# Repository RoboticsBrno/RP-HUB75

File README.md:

# RP2350 HUB75 Driver

Deska pro řízení HUB75 displejů založená na čipu [RP2350](https://www.raspberrypi.com/documentation/microcontrollers/silicon.html#rp2350)

<div style="display:grid; grid-template-columns:repeat(auto-fit,minmax(160px,1fr)); gap:1rem; align-items:start;">
    <figure>
        
        <figcaption>Front</figcaption>
    </figure>
    <figure>
        
        <figcaption>Back</figcaption>
    </figure>
</div>

Firmware a jeho dokumentace může být nalezen ve složce `sw/fw`. Mini driver pro pužití displaje pomocí USB je ve složce `sw/rawd`.

## Pinout

### Displej

| RP2350 | Displej | Displej | RP2350 |
|---:|:---|---:|:---|
| IO0  | R1  | G1  | IO1  |
| IO2  | B1  | GND | GND  |
| IO3  | R2  | G2  | IO4  |
| IO5  | B2  | E   | IO6  |
| IO7  | A   | B   | IO8  |
| IO9  | C   | D   | IO10 |
| IO11 | CLK | LAT | IO12 |
| IO13 | OE  | GND | GND  |

### Konektor

!!! note
    Je možno použít QSPI nebo SPI, v tom případě musí být TX na MISO/RX pinu master desky!
    
| Konektor (pin) | Signál | RP2350 |
|---:|---|:---|
| 1  | GND | GND  |
| 2  | 5V  | 5V   |
| 3  | 5V  | 5V   |
| 4  | D0  | IO19 |
| 5  | D1  | IO20 |
| 6  | D2  | IO21 |
| 7  | D3  | IO22 |
| 8  | GND | GND  |
| 9  | CS  | IO23 |
| 10 | CK  | IO24 |

### Extra konektor
- Na desce jsou vyvedené 2 extra datové piny na kterých je přístupné I2C a UART pro další rozšíření. (není implementováno)

| Pin | I2C | UART |
|---:|---|---|
| 14  | SDA  | TX  |
| 15  | SCL  | RX  |

### DBG & PWR Led
- Debug/status led - IO18
- Power led - 3V3

## Licence
Celý repositář je licencován pod MIT licencí s výjimkou složky `sw/fw`, která spadá pod licenci BSD-3-Clause.

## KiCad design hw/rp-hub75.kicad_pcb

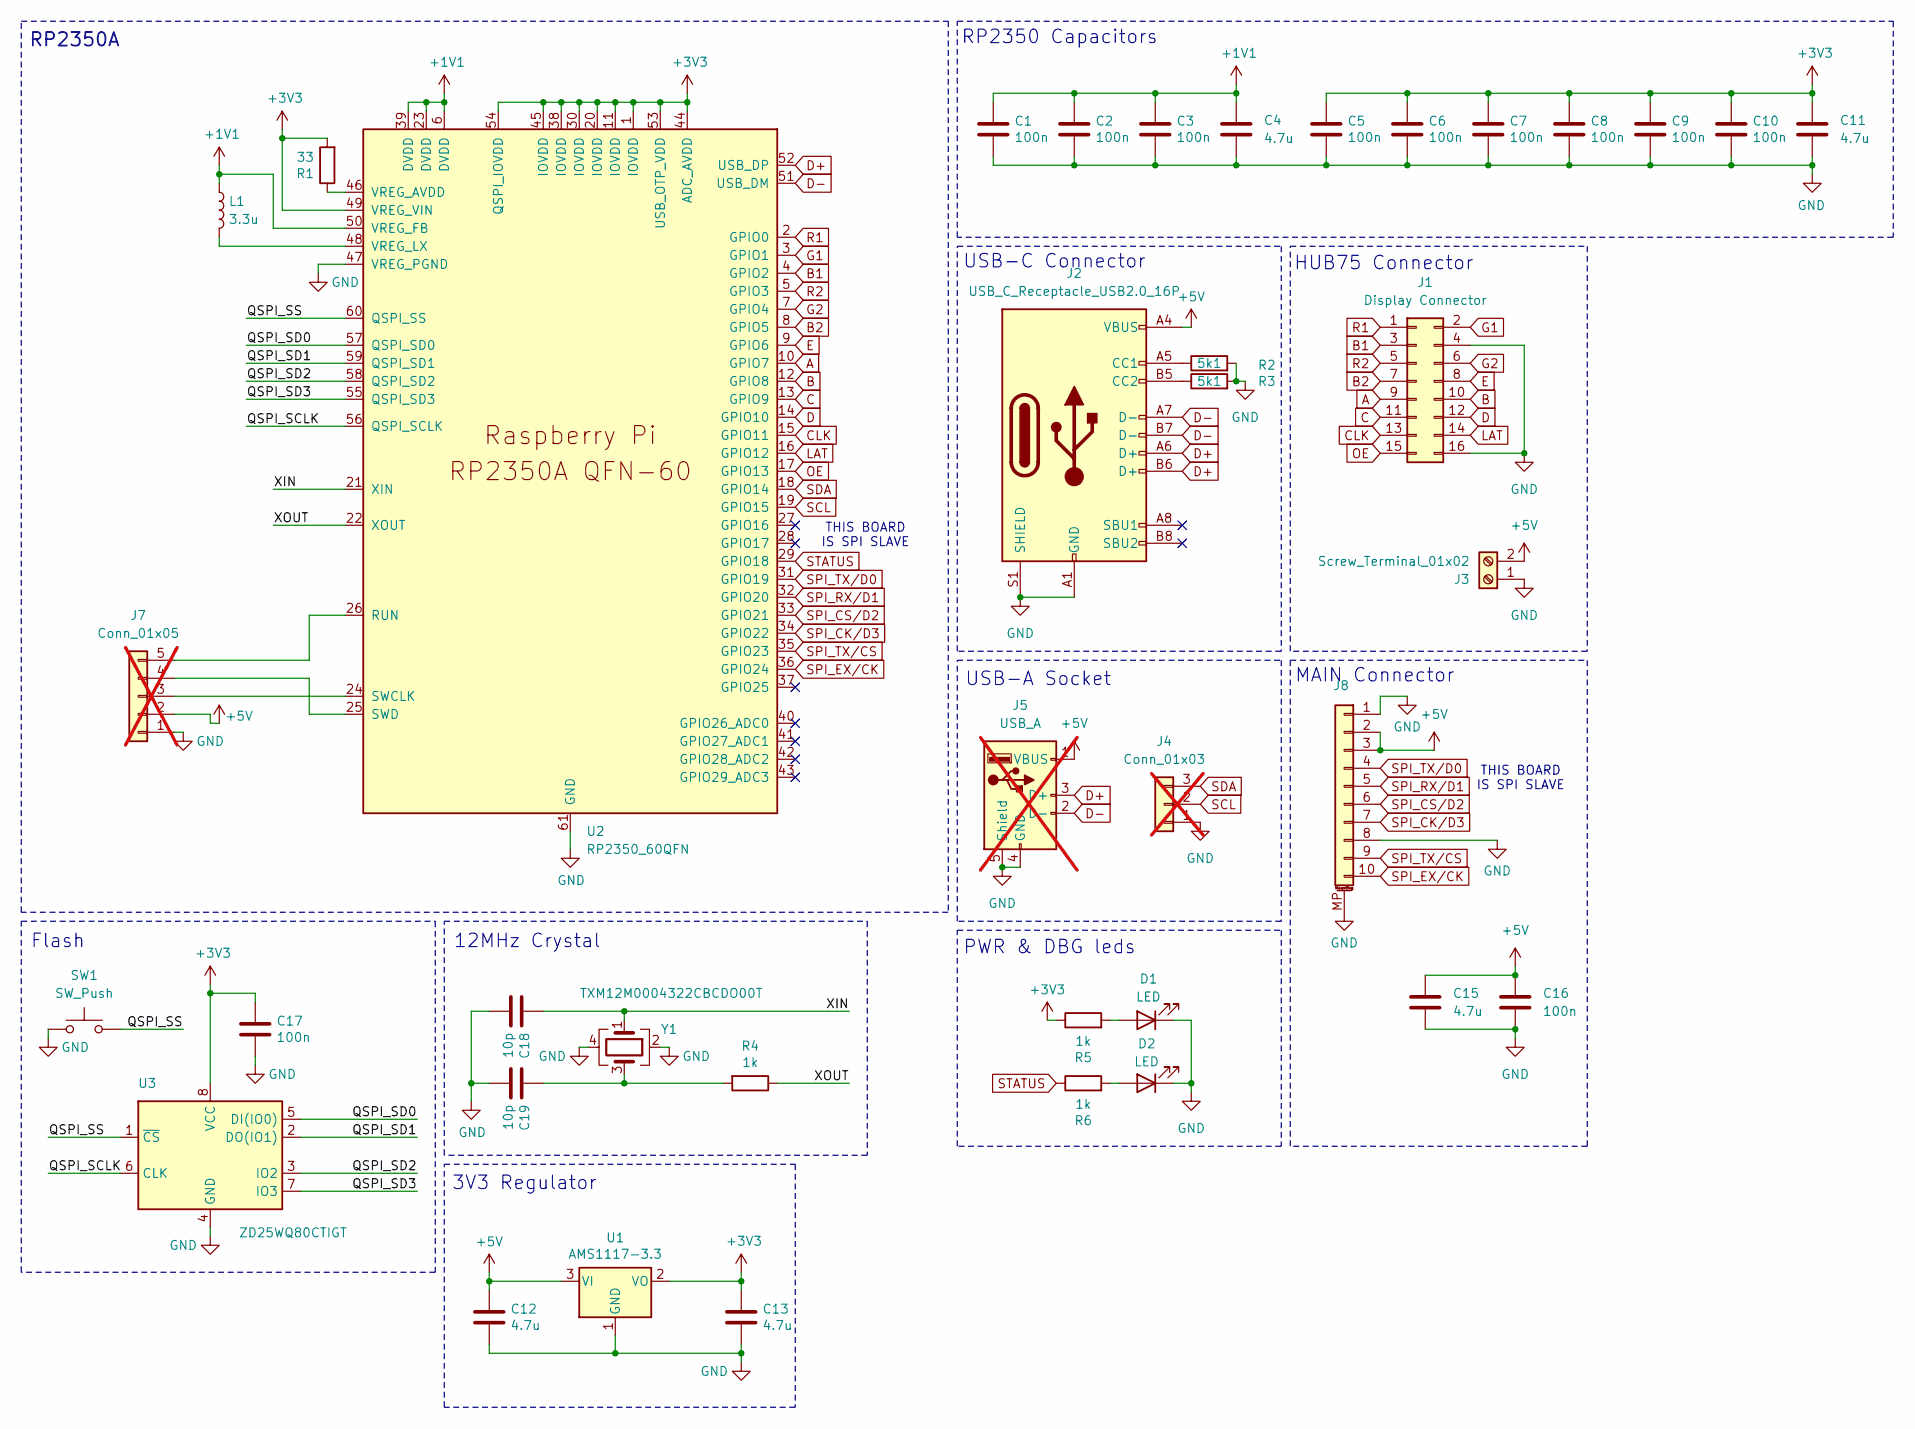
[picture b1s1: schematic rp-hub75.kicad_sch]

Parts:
C1, C2, C3, C5, C6, C7, C8, C9, C10, C16, C17: 100n; C_0402_1005Metric; LCSC C1525
C4, C11, C12, C13, C15: 4.7u; C_0805_2012Metric; LCSC C1779
C18, C19: 10p; C_0402_1005Metric; LCSC C32949
D1, D2: LED; LED_0805_2012Metric; LCSC C84256
J1: Display Connector; PinSocket_2x08_P2.54mm_Vertical; LCSC C30734
J2: USB_C_Receptacle_USB2.0_16P; USB_C_Receptacle_G-Switch_GT-USB-7010ASV; LCSC C2988369
J3: Screw_Terminal_01x02; TerminalBlock_Phoenix_MKDS-1,5-2-5.08_1x02_P5.08mm_Horizont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; LCSC C8465
J4: Conn_01x03; PinHeader_1x03_P2.54mm_Vertical; not fitted
J5: USB_A; USB_A_Kycon_KUSBX-AS1N-B_Horizontal; LCSC C2346; not fitted
J7: Conn_01x05; PinHeader_1x05_P2.54mm_Vertical; not fitted
J8: ZX-XH2.54-10PWT; JST-XH-SMD-10Pin; LCSC C7429679
L1: 3.3u; L_1008_2520Metric_Pad1.43x2.20mm_HandSolder; LCSC C337916
R1: 33; R_0402_1005Metric; LCSC C25105
R2, R3: 5k1; R_0402_1005Metric; LCSC C25905
R4, R5, R6: 1k; R_0402_1005Metric; LCSC C11702
SW1: SW_Push; SW_SPST_TS-1088-xR025; LCSC C720477
U1: AMS1117-3.3; SOT-223-3_TabPin2; LCSC C6186
U2: RP2350_60QFN; RP2350-QFN-60-1EP_7x7_P0.4mm_EP3.4x3.4mm_ThermalVias; LCSC C42411118
U3: ZD25WQ80CTIGT; SOIC-8_3.9x4.9mm_P1.27mm; LCSC C7525143
Y1: TXM12M0004322CBCDO00T; Crystal_SMD_3225-4Pin_3.2x2.5mm; LCSC C362368

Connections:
+1V1: C1.1, C2.1, C3.1, C4.1, L1.1, U2.6 (DVDD), U2.23 (DVDD), U2.39 (DVDD), U2.50 (VREG_FB)
+3V3: C5.1, C6.1, C7.1, C8.1, C9.1, C10.1, C11.1, C13.1, C17.1, R1.2, R5.1, U1.2 (VO), U2.1 (IOVDD), U2.11 (IOVDD), U2.20 (IOVDD), U2.30 (IOVDD), U2.38 (IOVDD), U2.44 (ADC_AVDD), U2.45 (IOVDD), U2.49 (VREG_VIN), U2.53 (USB_OTP_VDD), U2.54 (QSPI_IOVDD), U3.8 (VCC)
+5V: C12.1, C15.1, C16.1, J2.A4 (VBUS), J2.A9 (VBUS), J2.B4 (VBUS), J2.B9 (VBUS), J3.2, J5.1 (VBUS), J7.2, J8.2, J8.3, U1.3 (VI)
/QSPI_SCLK: U2.56 (QSPI_SCLK), U3.6 (CLK)
/QSPI_SD0: U2.57 (QSPI_SD0), U3.5 (DI(IO0))
/QSPI_SD1: U2.59 (QSPI_SD1), U3.2 (DO(IO1))
/QSPI_SD2: U2.58 (QSPI_SD2), U3.3 (IO2)
/QSPI_SD3: U2.55 (QSPI_SD3), U3.7 (IO3)
/QSPI_SS: SW1.2, U2.60 (QSPI_SS), U3.1 (~CS)
/XIN: C18.1, U2.21 (XIN), Y1.1
/XOUT: R4.1, U2.22 (XOUT)
A: J1.9, U2.10 (GPIO7)
B: J1.10, U2.12 (GPIO8)
B1: J1.3, U2.4 (GPIO2)
B2: J1.7, U2.8 (GPIO5)
C: J1.11, U2.13 (GPIO9)
CLK: J1.13, U2.15 (GPIO11)
D: J1.12, U2.14 (GPIO10)
D+: J2.A6 (D+), J2.B6 (D+), J5.3 (D+), U2.52 (USB_DP)
D-: J2.A7 (D-), J2.B7 (D-), J5.2 (D-), U2.51 (USB_DM)
E: J1.8, U2.9 (GPIO6)
G1: J1.2, U2.3 (GPIO1)
G2: J1.6, U2.7 (GPIO4)
GND: C1.2, C2.2, C3.2, C4.2, C5.2, C6.2, C7.2, C8.2, C9.2, C10.2, C11.2, C12.2, C13.2, C15.2, C16.2, C17.2, C18.2, C19.2, D1.1 (K), D2.1 (K), J1.4, J1.16, J2.A1 (GND), J2.A12 (GND), J2.B1 (GND), J2.B12 (GND), J2.S1 (SHIELD), J3.1, J4.1, J5.4 (GND), J5.5 (Shield), J7.1, J8.1, J8.8, J8.MP (MountPin), R2.2, R3.2, SW1.1, U1.1 (GND), U2.47 (VREG_PGND), U2.61 (GND), U3.4 (GND), Y1.2, Y1.4
LAT: J1.14, U2.16 (GPIO12)
unnamed: C19.1, R4.2, Y1.3
unnamed: D1.2 (A), R5.2
unnamed: D2.2 (A), R6.2
unnamed: J2.A5 (CC1), R2.1
unnamed: J2.B5 (CC2), R3.1
unnamed: J7.3, U2.24 (SWCLK)
unnamed: J7.4, U2.25 (SWD)
unnamed: J7.5, U2.26 (RUN)
unnamed: R1.1, U2.46 (VREG_AVDD)
unnamed: L1.2, U2.48 (VREG_LX)
OE: J1.15, U2.17 (GPIO13)
R1: J1.1, U2.2 (GPIO0)
R2: J1.5, U2.5 (GPIO3)
SCL: J4.2, U2.19 (GPIO15)
SDA: J4.3, U2.18 (GPIO14)
SPI_CK/D3: J8.7, U2.34 (GPIO22)
SPI_CS/D2: J8.6, U2.33 (GPIO21)
SPI_EX/CK: J8.10, U2.36 (GPIO24)
SPI_RX/D1: J8.5, U2.32 (GPIO20)
SPI_TX/CS: J8.9, U2.35 (GPIO23)
SPI_TX/D0: J8.4, U2.31 (GPIO19)
STATUS: R6.1, U2.29 (GPIO18)

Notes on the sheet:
THIS BOARD IS SPI SLAVE
HUB75 Connector
USB-A Socket
12MHz Crystal
PWR & DBG leds
USB-C Connector
3V3 Regulator
Flash
RP2350A
RP2350 Capacitors
MAIN Connector

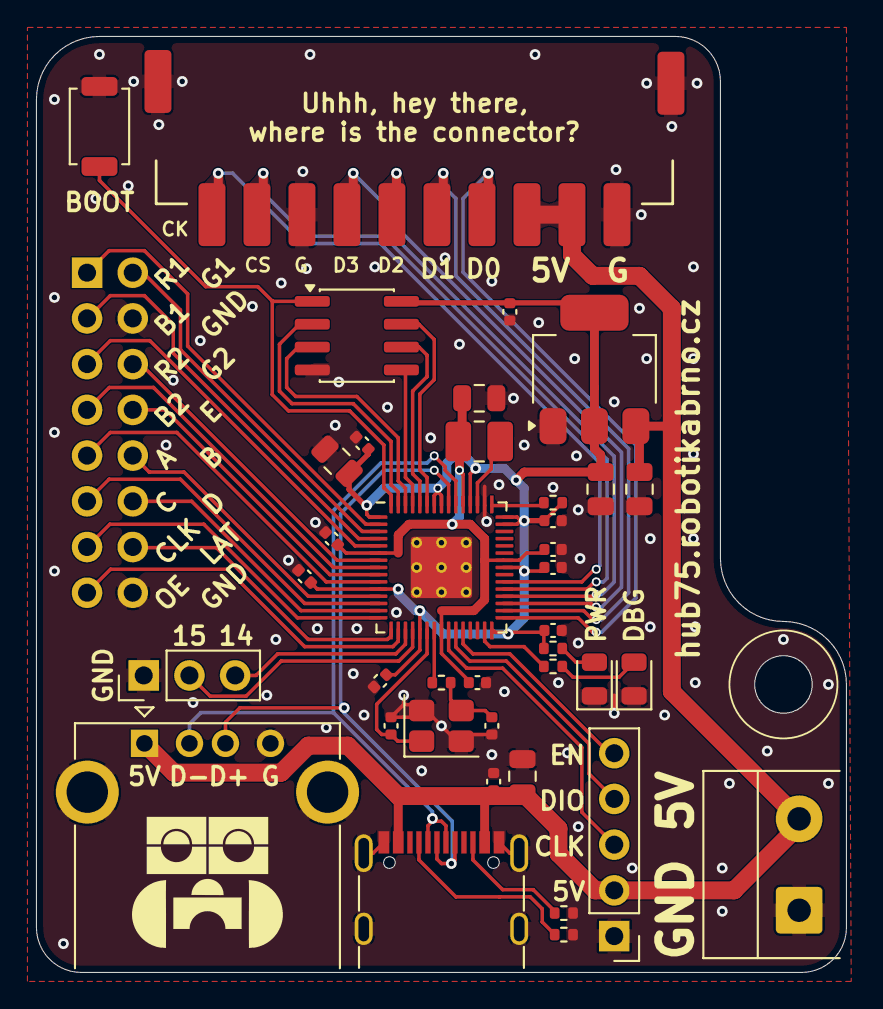
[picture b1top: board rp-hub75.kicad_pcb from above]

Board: 2 copper layers, 45.0 x 52.0 mm, 39 parts (1 on the bottom side), 47 nets.

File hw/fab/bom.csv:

Comment,Designator,Footprint,LCSC
ZD25WQ80CTIGT,U3,Package_SO:SOIC-8_3.9x4.9mm_P1.27mm,C7525143 
100n,"C1,C2,C3,C5,C6,C7,C8,C9,C10,C16,C17",Capacitor_SMD:C_0402_1005Metric,C1525
4.7u,"C4,C11,C12,C13,C15",Capacitor_SMD:C_0805_2012Metric,C1779
10p,"C18,C19",Capacitor_SMD:C_0402_1005Metric,C32949
USB_C_Receptacle_USB2.0_16P,J2,Connector_USB:USB_C_Receptacle_G-Switch_GT-USB-7010ASV,C2988369
RP2350_60QFN,U2,RP2350_60QFN_minimal:RP2350-QFN-60-1EP_7x7_P0.4mm_EP3.4x3.4mm_ThermalVias,C42411118 
Screw_Terminal_01x02,J3,"TerminalBlock_Phoenix:TerminalBlock_Phoenix_MKDS-1,5-2-5.08_1x02_P5.08mm_Horizontal",C8465
33,R1,Resistor_SMD:R_0402_1005Metric,C25105
LED,"D1,D2",LED_SMD:LED_0805_2012Metric,C84256
1k,"R4,R5,R6",Resistor_SMD:R_0402_1005Metric,C11702
5k1,"R2,R3",Resistor_SMD:R_0402_1005Metric,C25905
SW_Push,SW1,Button_Switch_SMD:SW_SPST_TS-1088-xR025,C720477
Display Connector,J1,Connector_PinSocket_2.54mm:PinSocket_2x08_P2.54mm_Vertical,C30734
3.3u,L1,Inductor_SMD:L_1008_2520Metric_Pad1.43x2.20mm_HandSolder,C337916
TXM12M0004322CBCDO00T,Y1,Crystal:Crystal_SMD_3225-4Pin_3.2x2.5mm,C362368
AMS1117-3.3,U1,Package_TO_SOT_SMD:SOT-223-3_TabPin2,C6186
ZX-XH2.54-10PWT,J8,Library:JST-XH-SMD-10Pin,C7429679

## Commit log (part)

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2025-10-29 Add files
2025-10-29 Deployed f63b39d with MkDocs version: 1.6.0
2025-10-29 docs: update readme
2025-10-29 Deployed 3daee73 with MkDocs version: 1.6.0
2025-11-01 WIP add fw, test-sw
2025-11-01 Deployed 836db96 with MkDocs version: 1.6.0
2025-11-01 hw: edit DBG connector, new capacitor
2025-11-05 update gitignore to fork
2025-11-05 wip: add first dev version of code
2025-11-05 feat: port moving circle from JohnieWalker
2025-11-05 feat: port platformer from JohnieWalker
2025-11-05 Deployed aa3a737 with MkDocs version: 1.6.0
2025-11-05 update: fw submodule
2025-11-05 Deployed b437e3b with MkDocs version: 1.6.0
2025-12-28 V1.2
2025-12-29 V1.3
2026-01-02 V1.4
2026-01-02 V1.4b
2026-01-04 Deployed 3a76ac7 with MkDocs version: 1.6.0
2026-01-25 fix: schematic cleanup
2026-01-26 feat: add protocol markup
2026-01-26 Deployed e69307c with MkDocs version: 1.6.0
2026-02-13 v1.5 - use QSPI, better 1V1 line
2026-02-13 Deployed 676e4a7 with MkDocs version: 1.6.0
2026-04-09 fw: initial driver firmware
2026-04-09 fw: WIP frame sync and lfsr sequence gen
2026-04-14 fw: tune protocol and add `proto.h` header
2026-04-15 sw/rawd: add `rawd` driver for pc usage
2026-04-15 fw: add misc build files and docs
2026-04-15 fw: add initial qspi rx driver
2026-04-21 fw: fixup the qspi backend
2026-04-21 fw: add support for gamma bypass + rgbx 32-bit format
2026-04-21 fw: add support for brightness control
2026-04-21 v1.6
2026-04-21 Deployed 00d114f with MkDocs version: 1.6.0
2026-05-15 v1.7
2026-05-15 Deployed 1a4c94d with MkDocs version: 1.6.0
2026-05-15 Deployed 9b38ac9 with MkDocs version: 1.6.0
2026-05-15 fix: Readme
    fixed pinout table
2026-05-15 Deployed 9ebd7bd with MkDocs version: 1.6.0
